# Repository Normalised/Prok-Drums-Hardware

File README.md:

# Prok-Drums-Hardware

Prok Drums are open hardware, they are a modified version of the Music Thing Modular Radio Music module by Tom Whitwell and have the Creative Commons license CC-BY-SA: Attribution / ShareAlike. 

If you use any work from this hardware, you should credit Tom Whitwell, and you must republish any changes you make under the same license. 

Please remove all references to Prok and Thonk from the PCB silkscreen and project name before republishing.

The names Prok and Thonk, their associated logos and module names are not open source and should not be used in any derivative works.

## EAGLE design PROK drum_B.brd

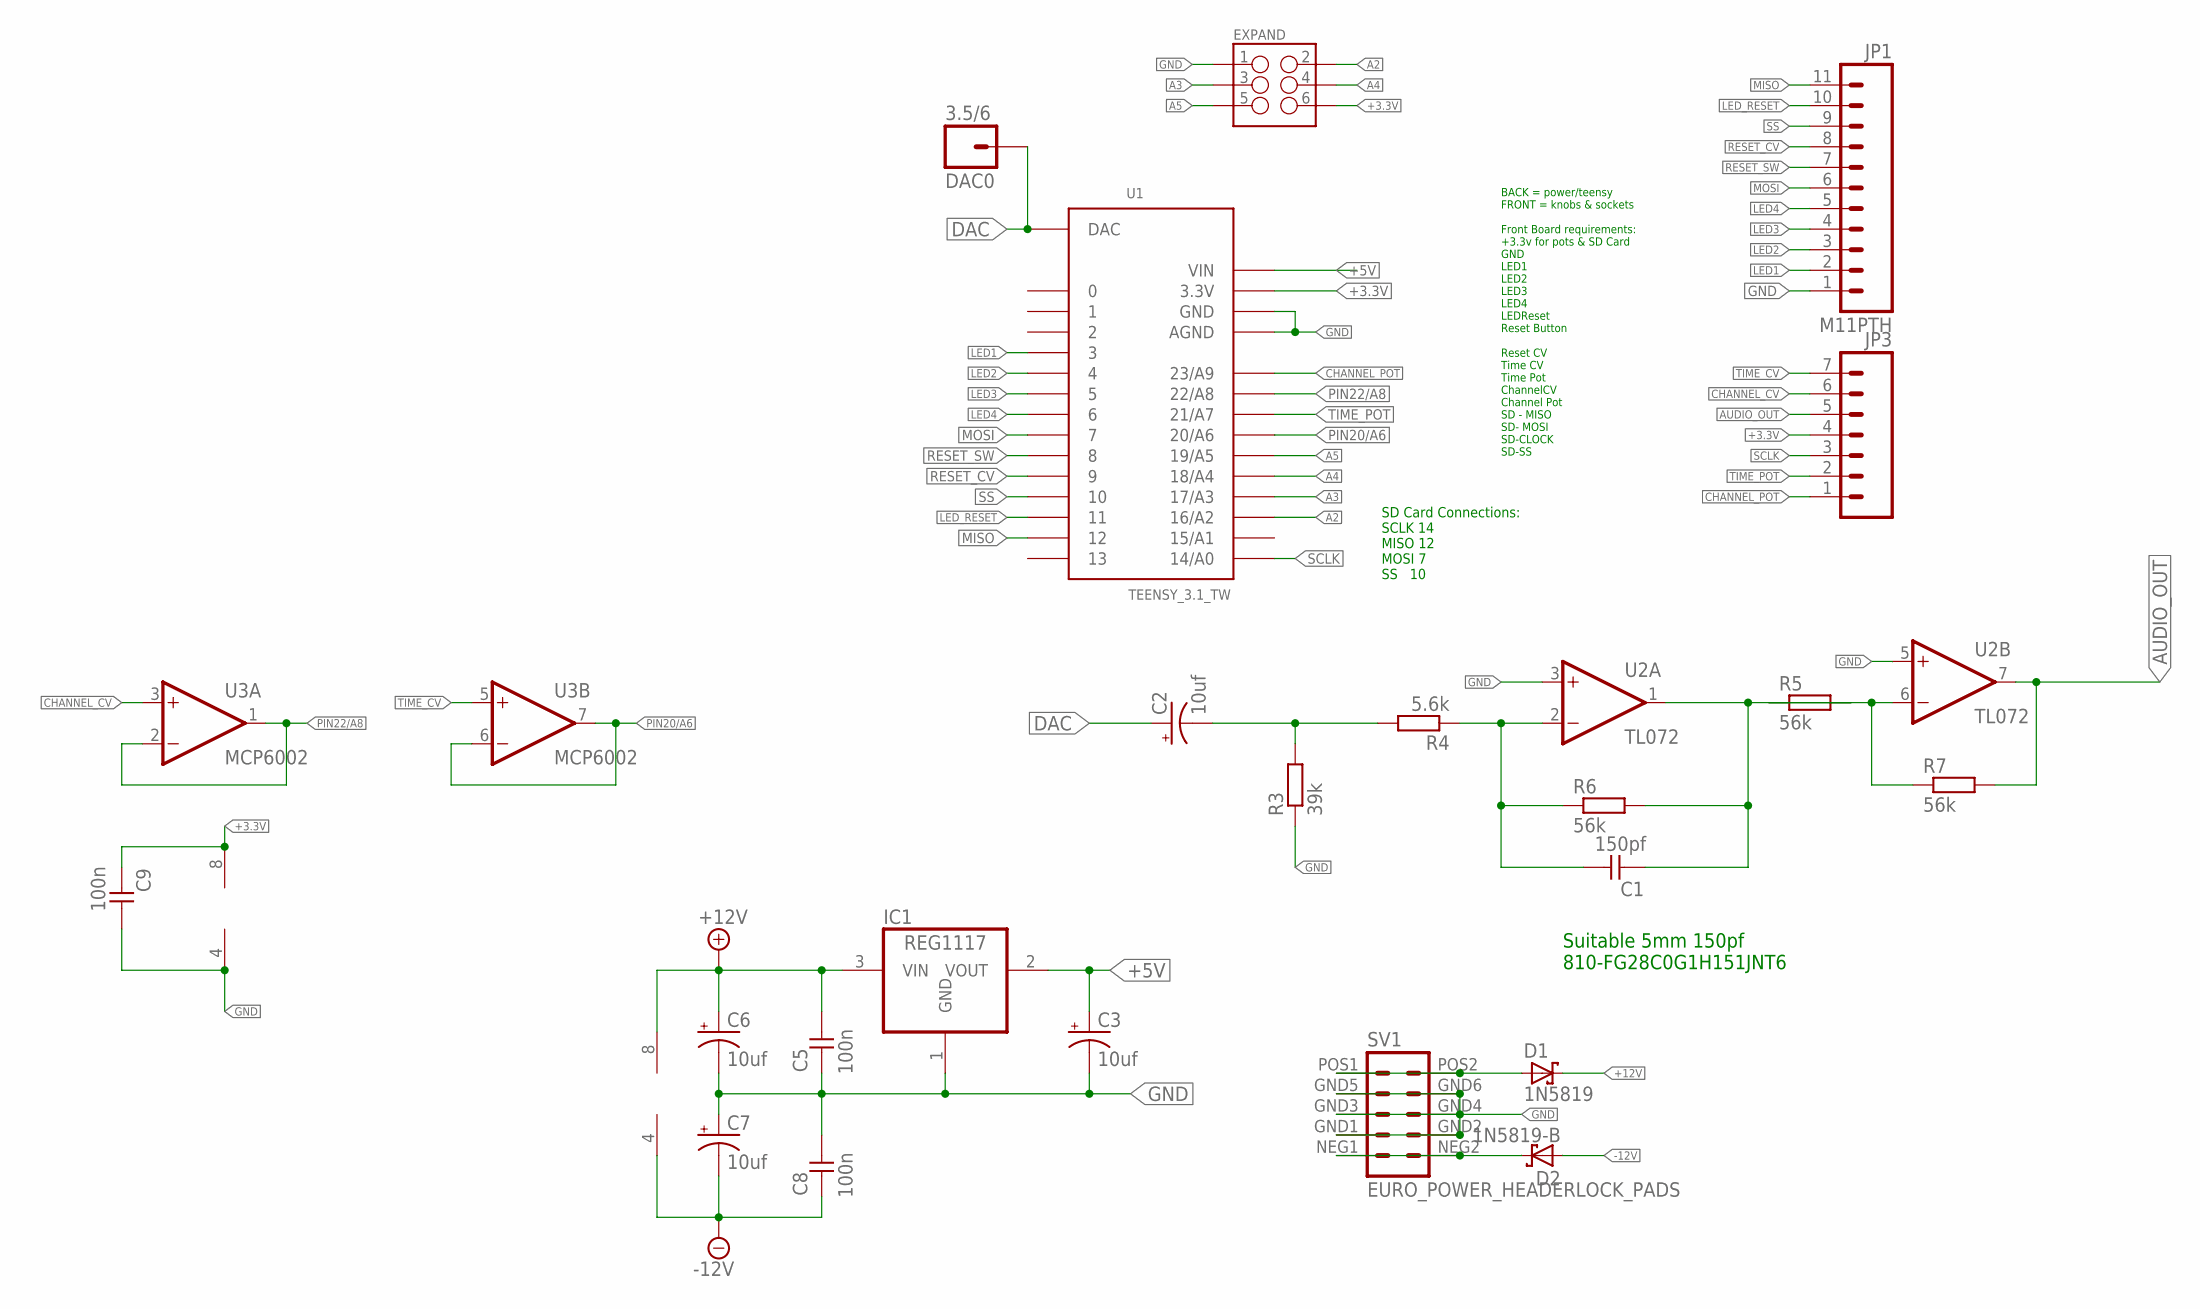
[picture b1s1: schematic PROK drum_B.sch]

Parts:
3.5/6: DAC0; 1X01
C1: 150pf; C050-024X044
C2, C3, C6, C7: 10uf; CPOL-RADIAL-10UF-25V
C5, C8, C9: 100n; C050-024X044
D1: 1N5819; DO41-7.6
D2: 1N5819-B; DO41-7.6
EXPAND: M03X22X3_SILK_SM; 2X3
IC1: REG1117; SOT223
JP1: M11PTH; 1X11
JP3: M07; 1X07
R3: 39k; 7MM_RESISTOR
R4: 5.6k; 7MM_RESISTOR
R5, R6, R7: 56k; 7MM_RESISTOR
SV1: EURO_POWER_HEADERLOCK_PADS; EURO_PWR_HEADER_LOCK
U1: TEENSY_3.1_TW
U2: TL072; DIL08-SML
U3: MCP6002; DIL08-SML

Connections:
+3.3V: C9.2, EXPAND.6, JP3.4, U1.3.3V, U3.8 (V+)
+5V: C3.1 (+), IC1.2 (VOUT), U1.VIN
+12V: C5.1, C6.1 (+), D1.C, IC1.3 (VIN), U2.8 (V+)
-12V: C7.2 (-), C8.2, D2.A, U2.4 (V-)
A2: EXPAND.2, U1.16/A2
A3: EXPAND.3, U1.17/A3
A4: EXPAND.4, U1.18/A4
A5: EXPAND.5, U1.19/A5
AUDIO_OUT: JP3.5, R7.2, U2.7 (OUT)
CHANNEL_CV: JP3.6, U3.3 (+IN)
CHANNEL_POT: JP3.1, U1.23/A9
DAC: 3.5/6.1, C2.1 (+), U1.DAC
GND: C3.2 (-), C5.2, C6.2 (-), C7.1 (+), C8.1, C9.1, EXPAND.1, IC1.1 (GND), JP1.1, R3.1, SV1.GND1 (4), SV1.GND2 (3), SV1.GND3 (6), SV1.GND4 (5), SV1.GND5 (8), SV1.GND6 (7), U1.AGND, U1.GND, U2.3 (+IN), U2.5 (+IN), U3.4 (V-)
LED1: JP1.2, U1.3
LED2: JP1.3, U1.4
LED3: JP1.4, U1.5
LED4: JP1.5, U1.6
LED_RESET: JP1.10, U1.11
MISO: JP1.11, U1.12
MOSI: JP1.6, U1.7
unnamed: C2.2 (-), R3.2, R4.2
unnamed: C1.1, R4.1, R6.1, U2.2 (-IN)
unnamed: R5.1, R7.1, U2.6 (-IN)
unnamed: C1.2, R5.2, R6.2, U2.1 (OUT)
unnamed: D1.A, SV1.POS1 (10), SV1.POS2 (9)
unnamed: D2.C, SV1.NEG1 (2), SV1.NEG2 (1)
PIN20/A6: U1.20/A6, U3.6 (-IN), U3.7 (OUT)
PIN22/A8: U1.22/A8, U3.1 (OUT), U3.2 (-IN)
RESET_CV: JP1.8, U1.9
RESET_SW: JP1.7, U1.8
SCLK: JP3.3, U1.14/A0
SS: JP1.9, U1.10
TIME_CV: JP3.7, U3.5 (+IN)
TIME_POT: JP3.2, U1.21/A7

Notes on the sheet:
SD Card Connections: SCLK 14 MISO 12 MOSI 7 SS 10
BACK = power/teensy FRONT = knobs & sockets Front Board requirements: +3.3v for pots & SD Card GND LED1 LED2 LED3 LED4 LEDReset Reset Button Reset CV Time CV Time Pot ChannelCV Channel Pot SD - MISO SD- MOSI SD-CLOCK SD-SS
Suitable 5mm 150pf 810-FG28C0G1H151JNT6

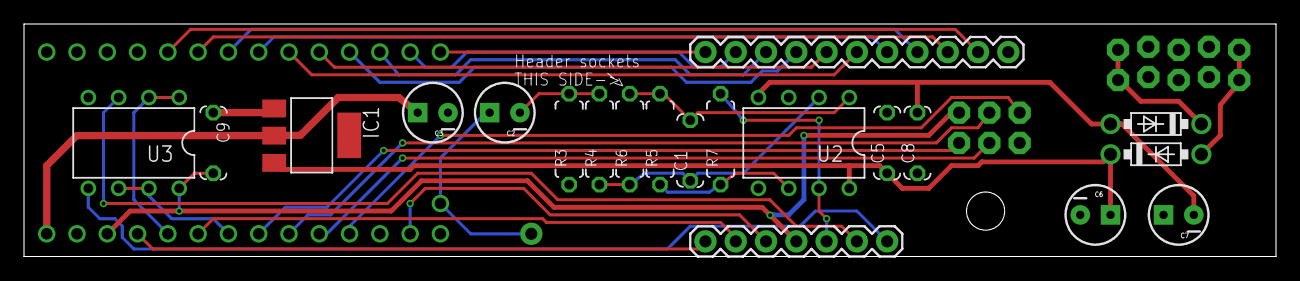
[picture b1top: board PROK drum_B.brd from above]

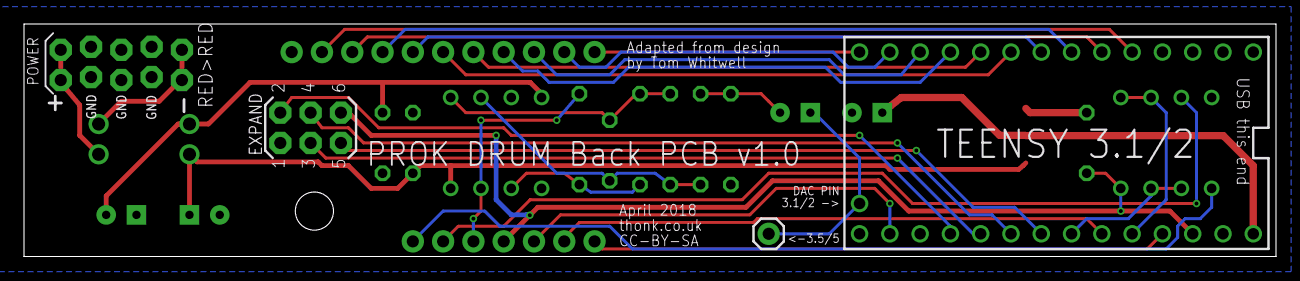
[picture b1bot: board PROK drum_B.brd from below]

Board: 4 copper layers, 105.0 x 19.5 mm, 25 parts (4 on the bottom side), 34 nets.

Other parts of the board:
U$1: MOUNTING_HOLE

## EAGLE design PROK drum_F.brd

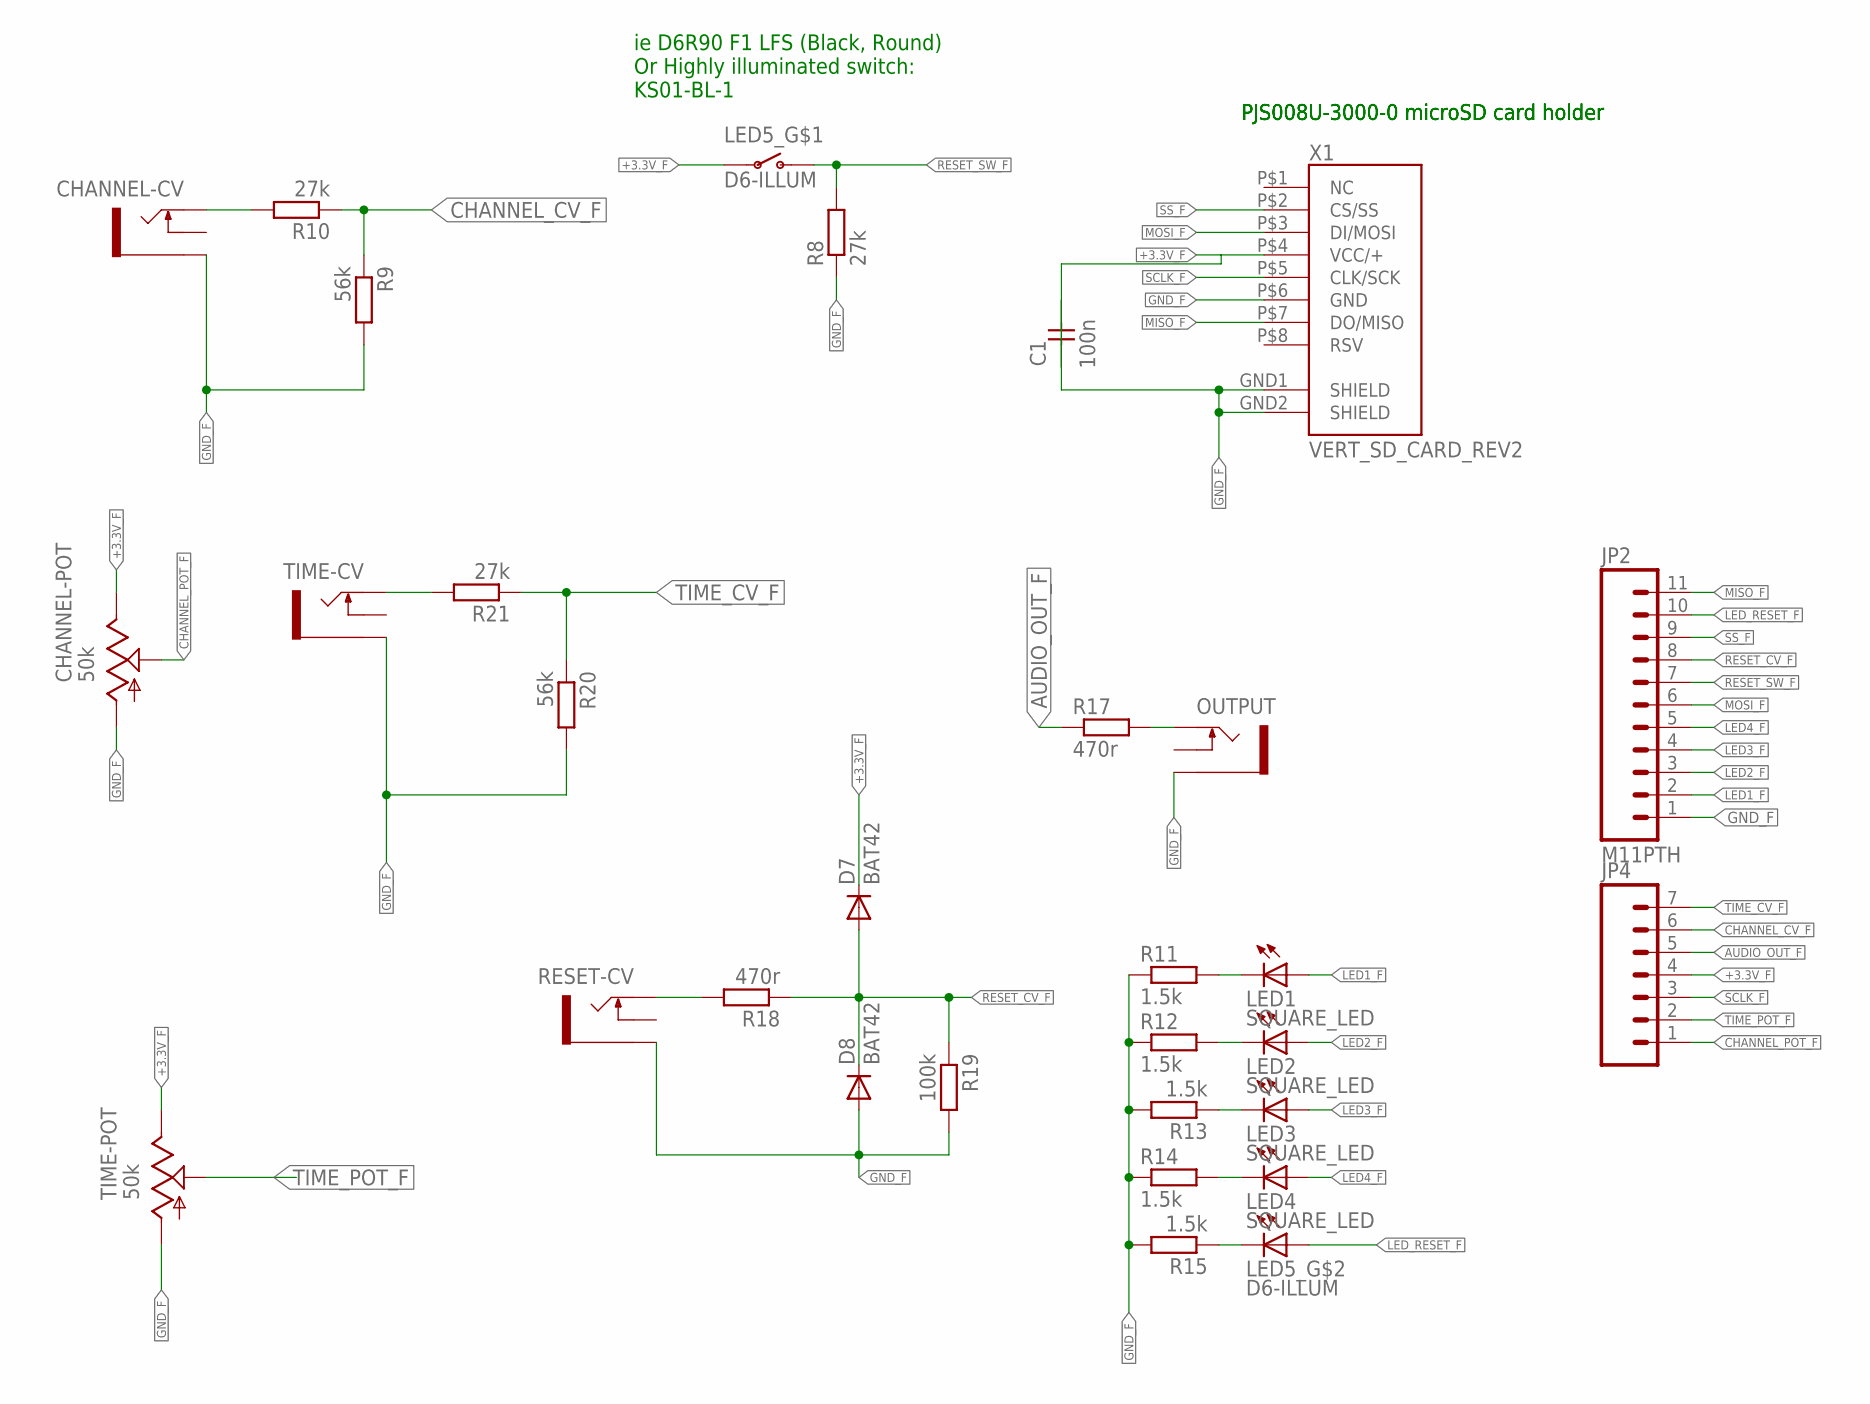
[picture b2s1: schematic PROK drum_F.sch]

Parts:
C1: 100n; C050-024X044
CHANNEL-CV: THONKICONNNEW; WQP-PJ301M-12_JACK
CHANNEL-POT: 50k; EVUF
D7, D8: BAT42; DO34-7
JP2: M11PTH; 1X11
JP4: M07; 1X07
LED1, LED2, LED3, LED4: SQUARE_LED
LED5_: D6-ILLUM; D6_PUSH_SWITCH_ILLUM
OUTPUT: THONKICONNNEW; WQP-PJ301M-12_JACK
R8: 27k; 7MM_RESISTOR
R9: 56k; 7MM_RESISTOR
R10, R21: 27k; VERTICAL_RESISTOR
R11, R12, R14, R15: 1.5k; 7MM_RESISTOR
R13: 1.5k; VERTICAL_RESISTOR
R17, R18: 470r; 7MM_RESISTOR
R19: 100k; 7MM_RESISTOR
R20: 56k; VERTICAL_RESISTOR
RESET-CV: THONKICONNNEW; WQP-PJ301M-12_JACK
TIME-CV: THONKICONNNEW; WQP-PJ301M-12_JACK
TIME-POT: 50k; EVUF
X1: VERT_SD_CARD_REV2; VERT_MICROSD_REV2

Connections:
+3.3V_F: C1.2, CHANNEL-POT.3 (E), D7.C, JP4.4, LED5_.P$3, LED5_.P$4, TIME-POT.3 (E), X1.P$4 (VCC/+)
AUDIO_OUT_F: JP4.5, R17.1
CHANNEL_CV_F: JP4.6, R9.1, R10.1
CHANNEL_POT_F: CHANNEL-POT.2 (S), JP4.1
GND_F: C1.1, CHANNEL-CV.P$3_SLEEVE (SLEEVE), CHANNEL-POT.1 (A), D8.A, JP2.1, OUTPUT.P$3_SLEEVE (SLEEVE), R8.1, R9.2, R11.1, R12.1, R13.2, R14.1, R15.2, R19.2, R20.2, RESET-CV.P$3_SLEEVE (SLEEVE), TIME-CV.P$3_SLEEVE (SLEEVE), TIME-POT.1 (A), X1.GND1 (SHIELD), X1.GND2 (SHIELD), X1.P$6 (GND)
LED1_F: JP2.2, LED1.ANODE (A)
LED2_F: JP2.3, LED2.ANODE (A)
LED3_F: JP2.4, LED3.ANODE (A)
LED4_F: JP2.5, LED4.ANODE (A)
LED_RESET_F: JP2.10, LED5_.LED+ (A)
MISO_F: JP2.11, X1.P$7 (DO/MISO)
MOSI_F: JP2.6, X1.P$3 (DI/MOSI)
unnamed: CHANNEL-CV.P$1_TIP (TIP), R10.2
unnamed: R21.2, TIME-CV.P$1_TIP (TIP)
unnamed: OUTPUT.P$1_TIP (TIP), R17.2
unnamed: R18.2, RESET-CV.P$1_TIP (TIP)
unnamed: LED1.CATHODE (C), R11.2
unnamed: LED2.CATHODE (C), R12.2
unnamed: LED3.CATHODE (C), R13.1
unnamed: LED4.CATHODE (C), R14.2
unnamed: LED5_.LED- (C), R15.1
RESET_CV_F: D7.A, D8.C, JP2.8, R18.1, R19.1
RESET_SW_F: JP2.7, LED5_.P$1 (O), LED5_.P$2 (O), R8.2
SCLK_F: JP4.3, X1.P$5 (CLK/SCK)
SS_F: JP2.9, X1.P$2 (CS/SS)
TIME_CV_F: JP4.7, R20.1, R21.1
TIME_POT_F: JP4.2, TIME-POT.2 (S)

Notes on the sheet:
ie D6R90 F1 LFS (Black, Round) Or Highly illuminated switch: KS01-BL-1
PJS008U-3000-0 microSD card holder

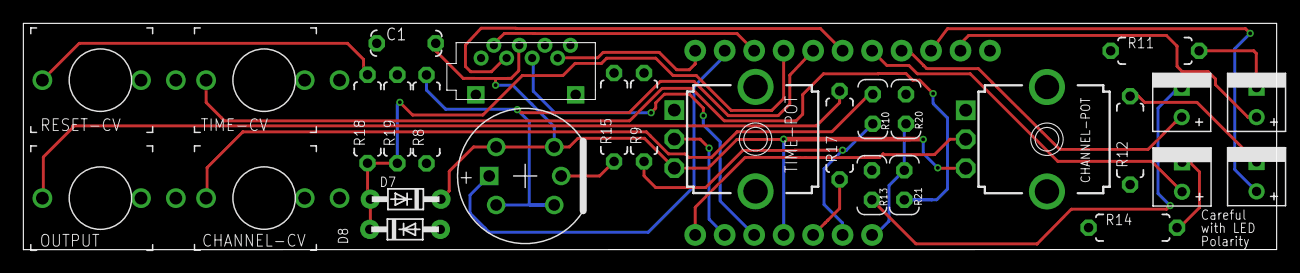
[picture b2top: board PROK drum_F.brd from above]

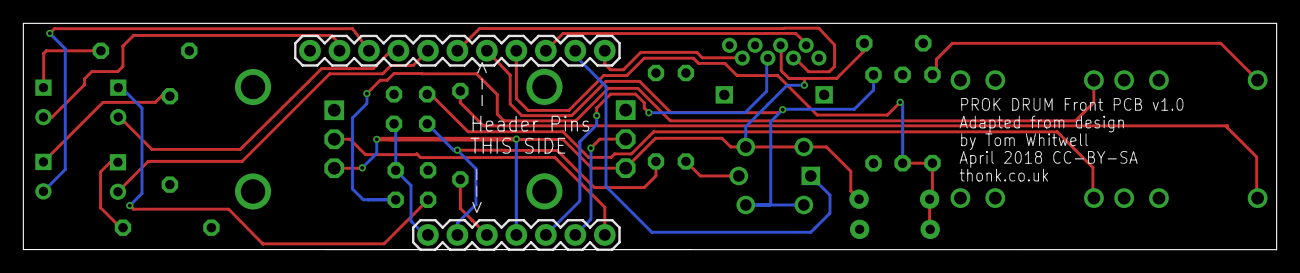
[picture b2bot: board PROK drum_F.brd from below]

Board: 4 copper layers, 108.0 x 19.5 mm, 30 parts (2 on the bottom side), 27 nets.

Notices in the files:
PROK drum_F.brd:
April 2018 CC-BY-SA
parts and their libraries:
SparkFun-Passives: Licensing: CC v3.0 Share-Alike You are welcome to use this library for commercial purposes.
